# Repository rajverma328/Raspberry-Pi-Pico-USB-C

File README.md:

# Custom Pi Pico Board Design

This repository contains the KiCAD design files for a custom-built Pi Pico board. The design was made entirely from scratch, utilizing KiCAD for PCB design and component placement. The board is based on the Raspberry Pi Pico microcontroller, featuring the RP2040 chip, and adheres to the original specifications with a few custom modifications.

## Project Overview

The Pi Pico is a low-cost, high-performance microcontroller board built around the Raspberry Pi RP2040 chip. This project involves creating a custom version of the Pi Pico using KiCAD, incorporating specific design requirements and optimizations.

### Key Features:
- **RP2040 Chip**: Dual-core ARM Cortex M0+ processor.
- **Custom PCB Layout**: Designed from scratch using KiCAD, following the original Pi Pico dimensions and pinout.
- **Minimalist Design**: Optimized for reduced footprint and enhanced performance.
- **I/O Accessibility**: Exposes GPIO pins for custom hardware interfacing.
- **Power Management**: Includes onboard power regulation for stable operation.
  
## Getting Started

### Prerequisites:
- **KiCAD**: Download and install [KiCAD](https://kicad.org/) to view and modify the design files.
- **RP2040 Documentation**: Refer to the [official RP2040 datasheet](https://www.raspberrypi.org/documentation/rp2040) for detailed information about the chip.
  
## Customizations

The board design can be customized in various ways:
- **Form Factor**: Adjust the board size or shape to suit specific requirements.
- **GPIO Configuration**: Modify the GPIO pin layout or functionality to match your project needs.
- **Power Supply**: Change the power input options or improve power management for different applications.

## Contributing

Contributions are welcome! If you have suggestions for improvements or additional features, feel free to open an issue or submit a pull request.

## License

This project is licensed under the MIT License. See the [LICENSE](./LICENSE) file for more details.

## Acknowledgments

- **Raspberry Pi Foundation**: For providing the RP2040 chip and the original Pi Pico design.
- **KiCAD Community**: For making an excellent open-source PCB design tool.

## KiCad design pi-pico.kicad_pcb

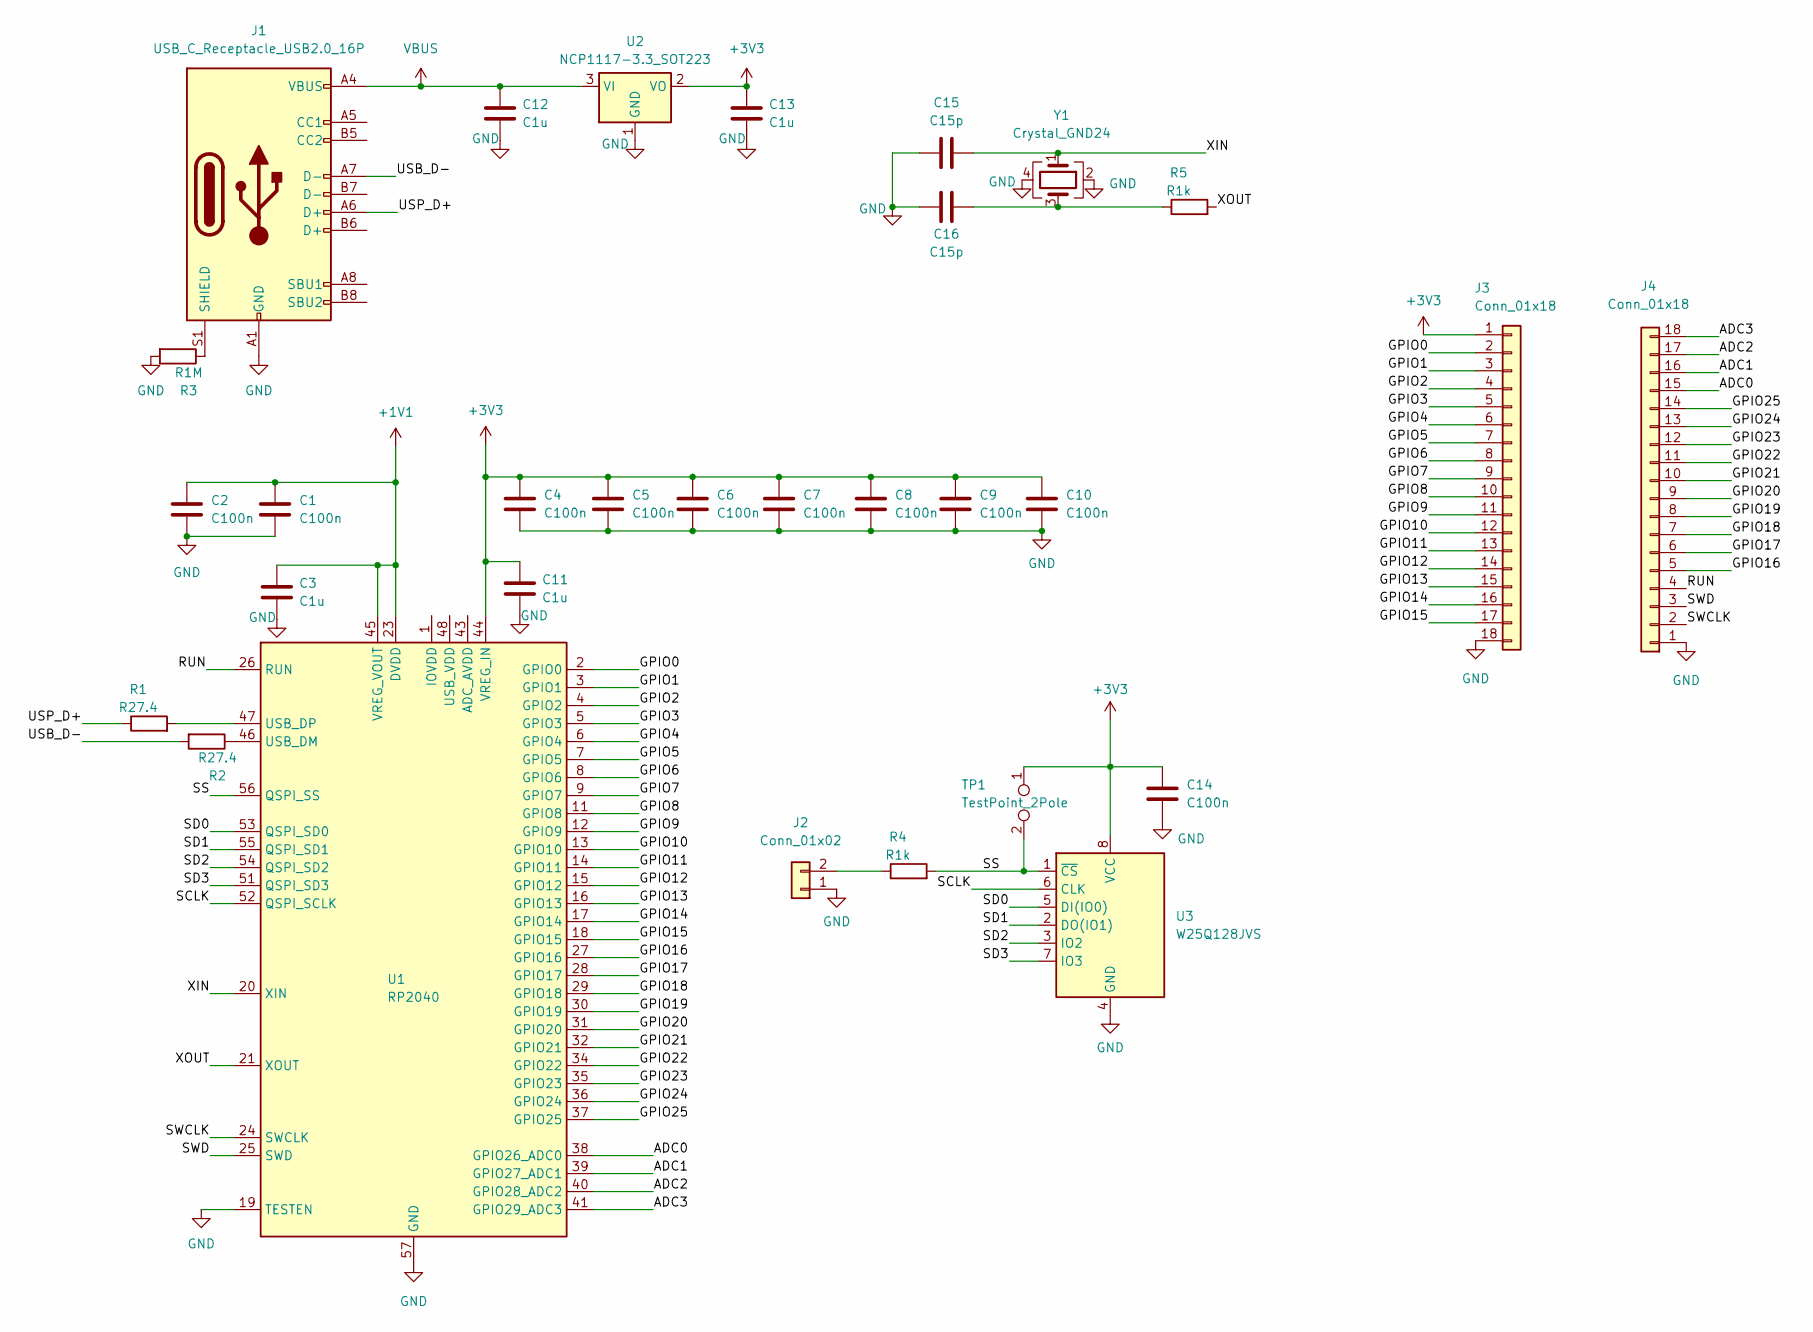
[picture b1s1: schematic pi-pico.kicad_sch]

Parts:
C1, C2, C4, C5, C6, C7, C8, C9, C10, C14: C100n; C_0402_1005Metric_Pad0.74x0.62mm_HandSolder
C3, C11, C12, C13: C1u; C_0402_1005Metric_Pad0.74x0.62mm_HandSolder
C15, C16: C15p; C_0402_1005Metric_Pad0.74x0.62mm_HandSolder
J1: USB_C_Receptacle_USB2.0_16P; USB_C_Receptacle_G-Switch_GT-USB-7010ASV
J2: Conn_01x02; PinHeader_1x02_P2.54mm_Vertical
J3, J4: Conn_01x18; PinHeader_1x18_P2.54mm_Vertical
R1, R2: R27.4; R_0402_1005Metric_Pad0.72x0.64mm_HandSolder
R3: R1M; R_0402_1005Metric_Pad0.72x0.64mm_HandSolder
R4, R5: R1k; R_0402_1005Metric_Pad0.72x0.64mm_HandSolder
TP1: TestPoint_2Pole; R_0201_0603Metric
U1: RP2040; QFN-56-1EP_7x7mm_P0.4mm_EP3.2x3.2mm
U2: NCP1117-3.3_SOT223; SOT-223-3_TabPin2
U3: W25Q128JVS; SOIC-8_5.23x5.23mm_P1.27mm
Y1: Crystal_GND24; Crystal_SMD_3225-4Pin_3.2x2.5mm

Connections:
+1V1: C1.1, C2.1, C3.1, U1.23 (DVDD), U1.45 (VREG_VOUT), U1.50 (DVDD)
+3V3: C4.1, C5.1, C6.1, C7.1, C8.1, C9.1, C10.1, C11.1, C13.1, C14.1, J3.1, TP1.1, U1.44 (VREG_IN), U2.2 (VO), U3.8 (VCC)
/ADC0: J4.15, U1.38 (GPIO26_ADC0)
/ADC1: J4.16, U1.39 (GPIO27_ADC1)
/ADC2: J4.17, U1.40 (GPIO28_ADC2)
/ADC3: J4.18, U1.41 (GPIO29_ADC3)
/GPIO0: J3.2, U1.2 (GPIO0)
/GPIO1: J3.3, U1.3 (GPIO1)
/GPIO2: J3.4, U1.4 (GPIO2)
/GPIO3: J3.5, U1.5 (GPIO3)
/GPIO4: J3.6, U1.6 (GPIO4)
/GPIO5: J3.7, U1.7 (GPIO5)
/GPIO6: J3.8, U1.8 (GPIO6)
/GPIO7: J3.9, U1.9 (GPIO7)
/GPIO8: J3.10, U1.11 (GPIO8)
/GPIO9: J3.11, U1.12 (GPIO9)
/GPIO10: J3.12, U1.13 (GPIO10)
/GPIO11: J3.13, U1.14 (GPIO11)
/GPIO12: J3.14, U1.15 (GPIO12)
/GPIO13: J3.15, U1.16 (GPIO13)
/GPIO14: J3.16, U1.17 (GPIO14)
/GPIO15: J3.17, U1.18 (GPIO15)
/GPIO16: J4.5, U1.27 (GPIO16)
/GPIO17: J4.6, U1.28 (GPIO17)
/GPIO18: J4.7, U1.29 (GPIO18)
/GPIO19: J4.8, U1.30 (GPIO19)
/GPIO20: J4.9, U1.31 (GPIO20)
/GPIO21: J4.10, U1.32 (GPIO21)
/GPIO22: J4.11, U1.34 (GPIO22)
/GPIO23: J4.12, U1.35 (GPIO23)
/GPIO24: J4.13, U1.36 (GPIO24)
/GPIO25: J4.14, U1.37 (GPIO25)
/RUN: J4.4, U1.26 (RUN)
/SCLK: U1.52 (QSPI_SCLK), U3.6 (CLK)
/SD0: U1.53 (QSPI_SD0), U3.5 (DI(IO0))
/SD1: U1.55 (QSPI_SD1), U3.2 (DO(IO1))
/SD2: U1.54 (QSPI_SD2), U3.3 (IO2)
/SD3: U1.51 (QSPI_SD3), U3.7 (IO3)
/SS: R4.2, TP1.2, U1.56 (QSPI_SS), U3.1 (~CS)
/SWCLK: J4.2, U1.24 (SWCLK)
/SWD: J4.3, U1.25 (SWD)
/USB_D-: J1.A7 (D-), R2.2
/USP_D+: J1.A6 (D+), R1.1
/XIN: C15.2, U1.20 (XIN), Y1.1
/XOUT: R5.2, U1.21 (XOUT)
GND: C1.2, C2.2, C3.2, C4.2, C5.2, C6.2, C7.2, C8.2, C9.2, C10.2, C11.2, C12.2, C13.2, C14.2, C15.1, C16.1, J1.A1 (GND), J1.A12 (GND), J1.B1 (GND), J1.B12 (GND), J2.1, J3.18, J4.1, R3.2, U1.19 (TESTEN), U1.57 (GND), U2.1 (GND), U3.4 (GND), Y1.2, Y1.4
unnamed: C16.2, R5.1, Y1.3
unnamed: J1.S1 (SHIELD), R3.1
unnamed: J2.2, R4.1
unnamed: U1.1 (IOVDD), U1.10 (IOVDD), U1.22 (IOVDD), U1.33 (IOVDD), U1.42 (IOVDD), U1.49 (IOVDD)
unnamed: R2.1, U1.46 (USB_DM)
unnamed: R1.2, U1.47 (USB_DP)
VBUS: C12.1, J1.A4 (VBUS), J1.A9 (VBUS), J1.B4 (VBUS), J1.B9 (VBUS), U2.3 (VI)

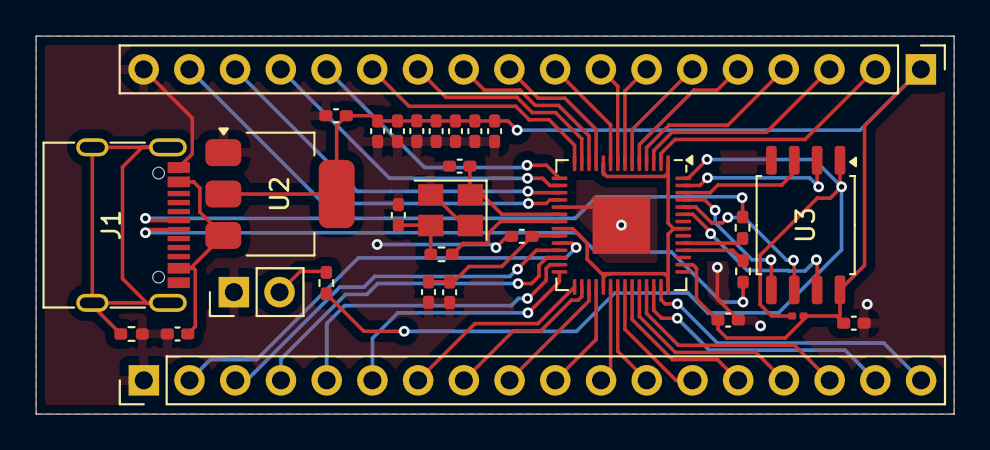
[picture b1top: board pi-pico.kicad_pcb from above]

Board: 2 copper layers, 51.0 x 21.0 mm, 30 parts (0 on the bottom side), 53 nets.

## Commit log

2024-10-13 Initial Schematic Initial README RESOURCES : 1
2024-10-13 IN progress Crysion Oscillator not yet configured
2024-10-14 COMPLETED
2024-10-14 README update
2024-10-14 Complete prokect
